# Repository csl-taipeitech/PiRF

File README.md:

# PiRF
A 2.4G Raspberry Pi nRF24L01 SPI module. [Order the borad on OSH Park!](https://oshpark.com/shared_projects/JfrGd6Lo)

## Fetures
- Support all model of Raspberry Pi (26-pin and 40-pin GPIO)
- On-board LED indicate IRQ of the nRF24
- Fit well with original Raspberry Pi Model B case

## Recommended libraries
RF24 has been tested by our team. Change the CE pin to GPIO24, IRQ to GPIO25 manually.
- [RF24](https://github.com/nRF24/RF24)

## Datasheet
- [GPIO and the 40-pin Header - Raspberry Pi Documentation](https://www.raspberrypi.com/documentation/computers/os.html#gpio-and-the-40-pin-header)
- [nRF24L01P_PS_v1.0.pdf - Nordic Semiconductor](https://infocenter.nordicsemi.com/pdf/nRF24L01P_PS_v1.0.pdf)
- [Ai-thinker NF-03 Specification](https://docs.ai-thinker.com/_media/nf-03_specification_en.pdf)

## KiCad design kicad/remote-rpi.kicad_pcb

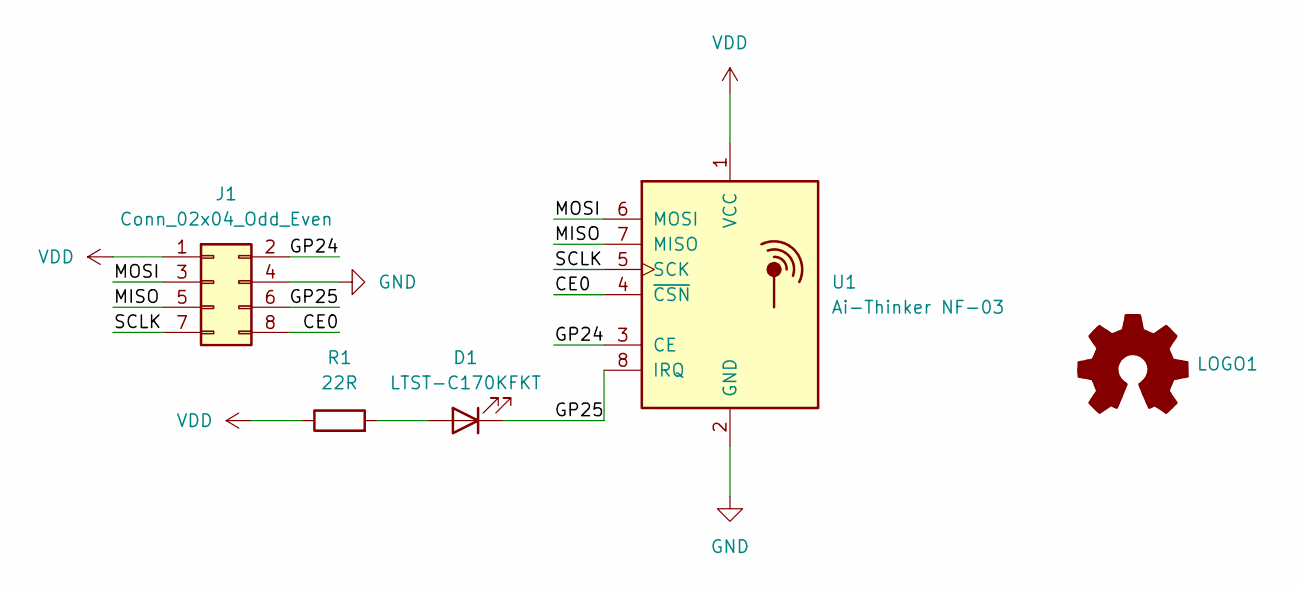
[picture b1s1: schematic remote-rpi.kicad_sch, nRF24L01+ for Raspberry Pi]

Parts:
D1: LTST-C170KFKT; LED_0805_2012Metric
J1: Conn_02x04_Odd_Even; PinSocket_2x04_P2.54mm_Vertical
LOGO1: Logo_Open_Hardware_Small; OSHW-Logo_5.7x6mm_SilkScreen
R1: 22R; R_0805_2012Metric
U1: Ai-Thinker NF-03; Ai-Thinker-NF-03

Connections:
/CE0: J1.8, U1.4 (~CSN)
/GP24: J1.2, U1.3 (CE)
/GP25: D1.1 (K), J1.6, U1.8 (IRQ)
/MISO: J1.5, U1.7 (MISO)
/MOSI: J1.3, U1.6 (MOSI)
/SCLK: J1.7, U1.5 (SCK)
GND: J1.4, U1.2 (GND)
unnamed: D1.2 (A), R1.2
VDD: J1.1, R1.1, U1.1 (VCC)

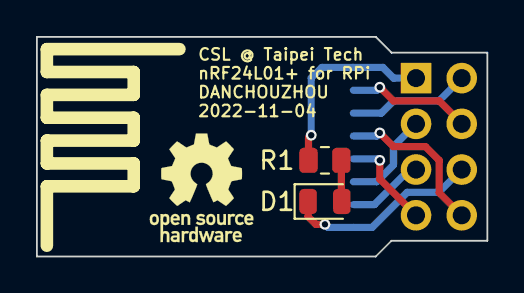
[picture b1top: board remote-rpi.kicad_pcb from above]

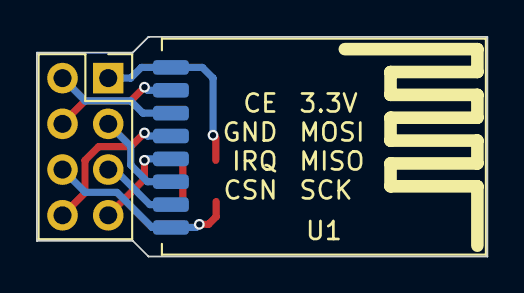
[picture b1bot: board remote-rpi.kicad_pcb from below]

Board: 2 copper layers, 25.0 x 12.2 mm, 5 parts (2 on the bottom side), 9 nets.

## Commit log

2022-11-16 Add photo
2022-11-16 Update image
2022-12-12 Does not fit Model A case

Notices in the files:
kicad/remote-rpi.kicad_sch:
Copyright © Danny Chou, all rights reserved.
